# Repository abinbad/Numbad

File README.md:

# Numbad
second** attempt at getting a macropad approved by Hack Club
# PCB
Designed in KiCad, it was really fun learning and designing the PDB!

# CAD
I actually designed it in Onshape ;P\

# Firmware
I am using the KMK Firmware, i just changed the pins i used on the board.
# Bill of Materials
Seeed XIAO RP2040 x1\
MX-Style Switches x9\
Blank DSA keycaps x9\
M3x16mm screws x1\
PCB x1\
3D Printeded Parts x2

⠀⠀⠀⠀⠀⠀⠀⠀⠀⠀⠀⠀⠀⠀⠀⠀⠀⠀⠀⠀⠀⠀⠀⢀⠀⠀⠀⠀⠀⠀⠀⠀⠀⠀⠀⠀⠀⠀⠀⠀⠀⠀⠀⠀⠀⠀⠀⠀⠀⠀⠀⠀⠀⠀⠀⠀⠀
⠀⠀⠀⠀⠀⠀⠀⠀⠀⠀⠀⠀⠀⠀⠀⠀⠀⠀⠀⠀⠀⢀⡴⠛⣧⠀⠀⠀⠀⠀⠀⠀⠀⠀⠀⠀⠀⠀⠀⠀⠀⠀⠀⠀⠀⠀⠀⠀⠀⠀⠀⠀⠀⠀⠀⠀⠀
⠀⠀⠀⠀⠀⠀⠀⠀⠀⠀⠀⠀⠀⠀⠀⠀⠀⠀⠀⠀⣰⠛⢠⡀⠸⣆⡀⠀⠀⠀⠀⠀⠀⠀⠀⠀⠀⠀⠀⠀⠀⠀⠀⠀⠀⠀⠀⠀⠀⠀⠀⠀⠀⠀⠀⠀⠀
⠀⠀⠀⠀⠀⠀⠀⠀⠀⠀⠀⠀⠀⠀⠀⠀⠀⠀⠀⡼⡁⢰⣋⡇⠀⡿⢳⡀⠀⠀⠀⠀⠀⠀⠀⠀⠀⠀⣠⠤⣀⣀⠀⠀⠀⠀⠀⠀⠀⠀⠀⠀⠀⠀⠀⠀⠀
⠀⠀⠀⠀⠀⠀⠀⠀⠀⠀⠀⠀⠀⠀⠀⠀⠀⠀⡼⠁⣏⠉⠛⠳⢤⣟⠀⢧⠀⠀⣀⣤⣠⣤⣄⣀⠀⠀⢷⠀⠀⠈⠙⠢⣄⠀⠀⠀⠀⠀⠀⠀⠀⠀⠀⠀⠀
⠀⠀⠀⠀⠀⠀⠀⠀⠀⠀⠀⠀⠀⠀⠀⠀⢰⡔⠃⣀⠘⢆⣀⠀⠀⠉⠀⠘⠚⠉⠀⠀⢀⡀⠀⢸⠇⣀⢸⡀⠀⠀⠀⠀⠈⢧⠀⠀⠀⠀⠀⠀⠀⠀⠀⠀⠀
⠀⠀⠀⠀⠀⠀⠀⠀⠀⠀⠀⠀⠀⠀⠀⠀⢹⠙⡾⠟⣷⠂⠉⠀⠀⠀⠀⠀⠀⠀⢶⢚⣹⠃⢠⡏⠀⡏⠹⠃⠀⠀⠀⠀⠀⢸⡆⠀⠀⠀⠀⠀⠀⠀⠀⠀⠀
⢀⣀⠀⠀⠀⠀⠀⠀⠀⠀⠀⠀⠀⠀⠀⠀⢸⣼⠇⣰⠀⠀⠀⠠⠶⠳⣦⠀⠀⠀⠘⠲⠃⢠⠟⠁⠀⡏⠀⠀⠀⠀⠀⠀⠀⢸⡇⠀⠀⠀⠀⠀⠀⠀⠀⠀⠀
⠈⣿⣷⣄⠀⠀⠀⠀⠀⠀⠀⠀⠀⠀⠀⢠⠏⡟⠷⠟⠁⠀⠀⣴⡆⠀⢸⡇⠀⠀⢠⣄⡴⠏⠀⡀⢰⠇⠀⠀⠀⠀⠀⠀⢠⡾⠚⠋⠉⠉⢳⡀⠀⠀⠀⠀⠀
⠀⢹⡌⠙⢷⣄⠀⠀⠀⠀⠀⠀⠀⠀⠀⠈⠉⢧⡐⠶⠄⠀⠀⠻⣃⡀⠸⡷⠀⠀⠀⠹⣆⠀⢀⡿⡏⠀⠀⠀⠀⠀⠀⣠⡾⠀⠀⠀⢀⡴⠟⠁⠀⠀⠀⠀⠀
⠀⠀⢷⠀⠀⠻⣷⣄⠀⠀⠀⠀⠀⠀⢀⣀⡀⠀⠙⠦⣤⣀⡀⠀⠘⠿⠇⠀⣤⠴⣶⣞⣁⣠⣾⡀⠀⠀⣤⣠⣴⠶⢾⣁⣧⠀⠀⠀⠈⢧⡤⠖⠚⠦⣄⡀⠀
⠀⠀⠘⡇⠀⠀⠈⠻⣷⡀⠀⠀⣠⢾⡉⢉⡍⠙⠳⣶⢟⣯⣭⠿⠷⣤⡀⣠⠏⠀⠀⠀⠀⠀⠀⠀⠀⠀⠀⠈⠉⠉⠛⠚⠻⠀⠀⠀⠀⠈⣇⠀⠀⠀⠀⠙⣦
⠀⠀⠀⢹⡀⠀⠀⠀⢿⣧⠀⠀⢧⣸⡀⠘⣇⣴⠀⠀⢘⠛⠛⠀⣰⠊⠻⠁⠀⠀⠀⠀⠀⠀⠀⠀⠀⠀⠀⠀⠀⠀⠀⠀⠀⠀⠀⠀⠀⠀⢹⣤⣄⣄⡓⣶⠏
⠀⠀⠀⠀⣧⠀⠀⠀⠈⣿⣆⣠⣤⣭⡭⠿⣹⣿⡋⠉⠛⠓⠒⠴⠃⠀⠀⠀⠀⢠⠀⠀⠀⠀⠀⠀⠀⠀⠀⠀⠀⠀⠀⠀⠀⠀⠀⠀⠀⠀⠠⣇⠈⠙⠛⠁⠀
⠀⠀⠀⠀⠈⠳⣄⠀⠀⠸⣿⠉⠀⠈⢻⠞⠙⡾⠁⡀⠀⠀⠀⠀⠀⠀⠀⠀⢀⣿⣀⣀⣀⣀⣀⣀⣀⣬⠷⠶⠤⢤⣤⣄⣀⣀⣤⣄⡀⣰⠤⢽⠆⠀⠀⠀⠀
⠀⠀⠀⠀⠀⠀⠈⠳⣄⠀⢿⣧⠀⠀⠘⠷⠾⠷⣼⣅⣀⣀⠀⠀⠀⠀⠀⠀⠸⡅⠀⠀⠉⠉⠁⠀⠀⠀⠀⠀⠀⠀⠀⠀⠀⠀⠀⠀⠙⠏⠀⠀⠀⠀⠀⠀⠀
⠀⠀⠀⠀⠀⠀⠀⠀⠘⢧⡈⡿⣄⣀⣀⣀⣀⣀⣈⣳⣍⠉⠉⠛⢿⡛⢦⡼⠛⠛⠀⠀⠀⠀⠀⠀⠀⠀⠀⠀⠀⠀⠀⠀⠀⠀⠀⠀⠀⠀⠀⠀⠀⠀⠀⠀⠀
⠀⠀⠀⠀⠀⠀⠀⠀⠀⠀⠙⠻⠻⠶⠿⠿⠷⠷⠿⠿⠾⠶⠶⠶⠶⠿⠟⠁⠀⠀⠀⠀⠀⠀⠀⠀⠀⠀⠀⠀⠀⠀⠀⠀⠀⠀⠀⠀⠀⠀⠀⠀⠀⠀⠀⠀⠀

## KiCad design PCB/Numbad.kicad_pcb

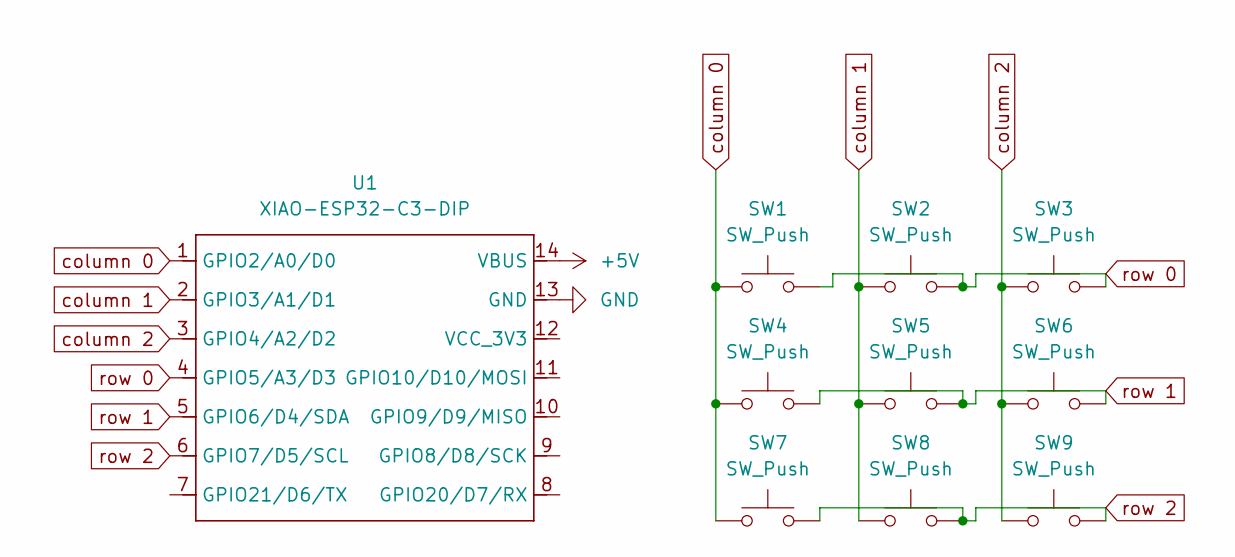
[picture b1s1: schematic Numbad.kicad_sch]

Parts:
SW1, SW2, SW3, SW4, SW5, SW6, SW7, SW8, SW9: SW_Push; SW_Cherry_MX_1.00u_PCB
U1: XIAO-ESP32-C3-DIP; XIAO-RP2040-DIP

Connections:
+5V: U1.14 (VBUS)
GND: U1.13 (GND)
column 0: SW1.1, SW4.1, SW7.1, U1.1 (GPIO2/A0/D0)
column 1: SW2.1, SW5.1, SW8.1, U1.2 (GPIO3/A1/D1)
column 2: SW3.1, SW6.1, SW9.1, U1.3 (GPIO4/A2/D2)
row 0: SW1.2, SW2.2, SW3.2, U1.4 (GPIO5/A3/D3)
row 1: SW4.2, SW5.2, SW6.2, U1.5 (GPIO6/D4/SDA)
row 2: SW7.2, SW8.2, SW9.2, U1.6 (GPIO7/D5/SCL)

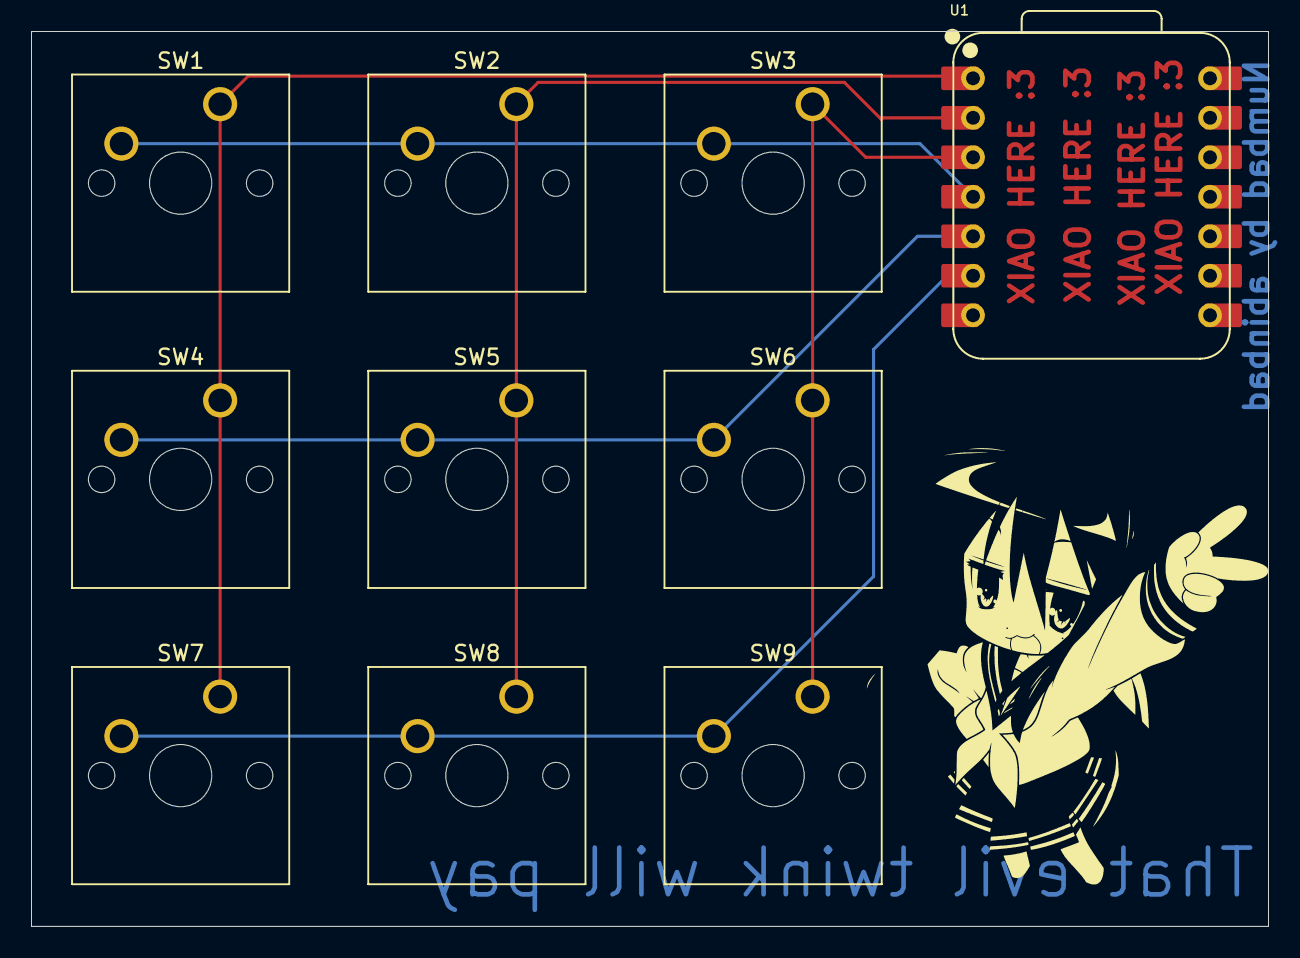
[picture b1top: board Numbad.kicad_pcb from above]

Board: 2 copper layers, 79.6 x 57.6 mm, 10 parts (0 on the bottom side), 6 nets.

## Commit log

2026-01-31 there is now things in here
2026-02-01 there is now a single cad file
2026-02-01 eddited README
2026-02-01 added line breaks(?)
2026-02-01 changed a thing in README
2026-02-01 removed some images
2026-02-01 there are now images in README
2026-02-03 there are now cad files
